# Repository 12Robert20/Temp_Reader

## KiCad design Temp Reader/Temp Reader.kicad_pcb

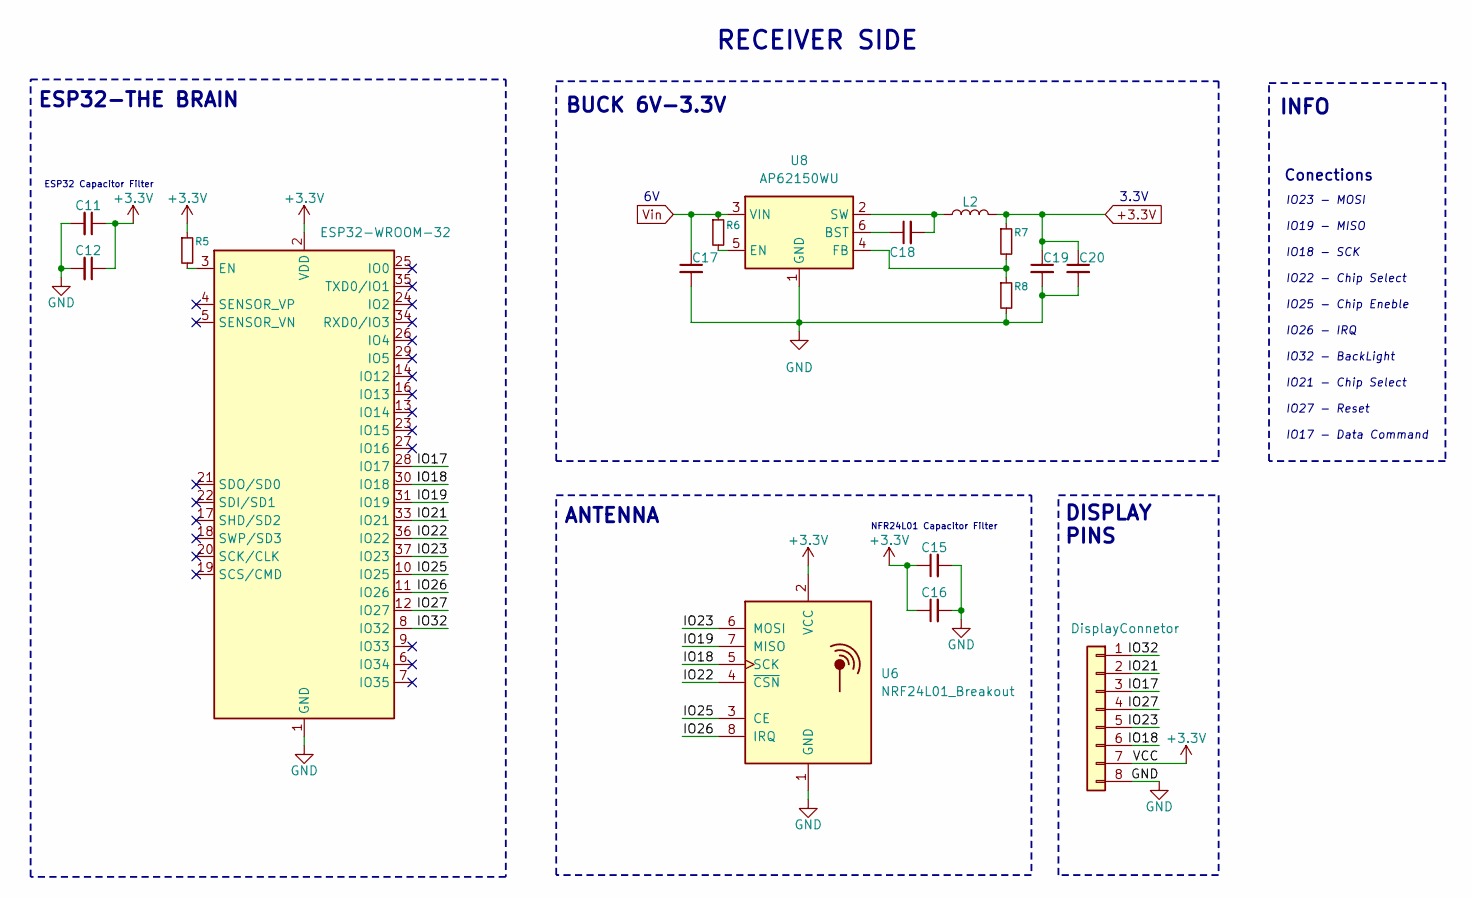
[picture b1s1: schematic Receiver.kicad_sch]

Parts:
C11, C15, C18: 100nF; C_0201_0603Metric
C12, C16: 10uF; C_1206_3216Metric
C17, C19, C20: 22uF; C_1206_3216Metric
J1: DisplayConnetor; PinSocket_1x08_P1.27mm_Vertical
L2: 2.2 uH; L_Bourns-SRN4018
R5, R8: 10k; R_0201_0603Metric
R6: 100k; R_0201_0603Metric
R7: 31.25k; R_0201_0603Metric
U3: ESP32-WROOM-32
U6: NRF24L01_Breakout; nRF24L01_Breakout
U8: AP62150WU; TSOT-23-6

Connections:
+3.3V: C11.1, C12.1, C15.1, C16.1, C19.1, C20.1, J1.7, L2.2, R5.1, R7.1, U3.2 (VDD), U6.2 (VCC); also elsewhere on the board
/Receiver Side/IO18: J1.6, U3.30 (IO18), U6.5 (SCK)
/Receiver Side/IO19: U3.31 (IO19), U6.7 (MISO)
/Receiver Side/IO21: J1.2, U3.33 (IO21)
/Receiver Side/IO22: U3.36 (IO22), U6.4 (~CSN)
/Receiver Side/IO23: J1.5, U3.37 (IO23), U6.6 (MOSI)
/Receiver Side/IO25: U3.10 (IO25), U6.3 (CE)
/Receiver Side/IO26: U3.11 (IO26), U6.8 (IRQ)
/Receiver Side/IO32: J1.1, U3.8 (IO32)
GND: C11.2, C12.2, C15.2, C16.2, C17.2, C19.2, C20.2, J1.8, R8.2, U3.1 (GND), U3.15 (GND), U3.38 (GND), U3.39 (GND), U6.1 (GND), U8.1 (GND); also elsewhere on the board
unnamed: R5.2, U3.3 (EN)
unnamed: C18.1, U8.6 (BST)
unnamed: R6.2, U8.5 (EN)
unnamed: R7.2, R8.1, U8.4 (FB)
unnamed: C18.2, L2.1, U8.2 (SW)
Vin: C17.1, R6.1, U8.3 (VIN); also elsewhere on the board

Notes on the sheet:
DISPLAY PINS
RECEIVER SIDE
IO23 - MOSI IO19 - MISO IO18 - SCK IO22 - Chip Select IO25 - Chip Eneble IO26 - IRQ IO32 - BackLight IO21 - Chip Select IO27 - Reset IO17 - Data Command
INFO
ESP32-THE BRAIN
Conections
ANTENNA
ESP32 Capacitor Filter
3.3V
BUCK 6V-3.3V
NFR24L01 Capacitor Filter

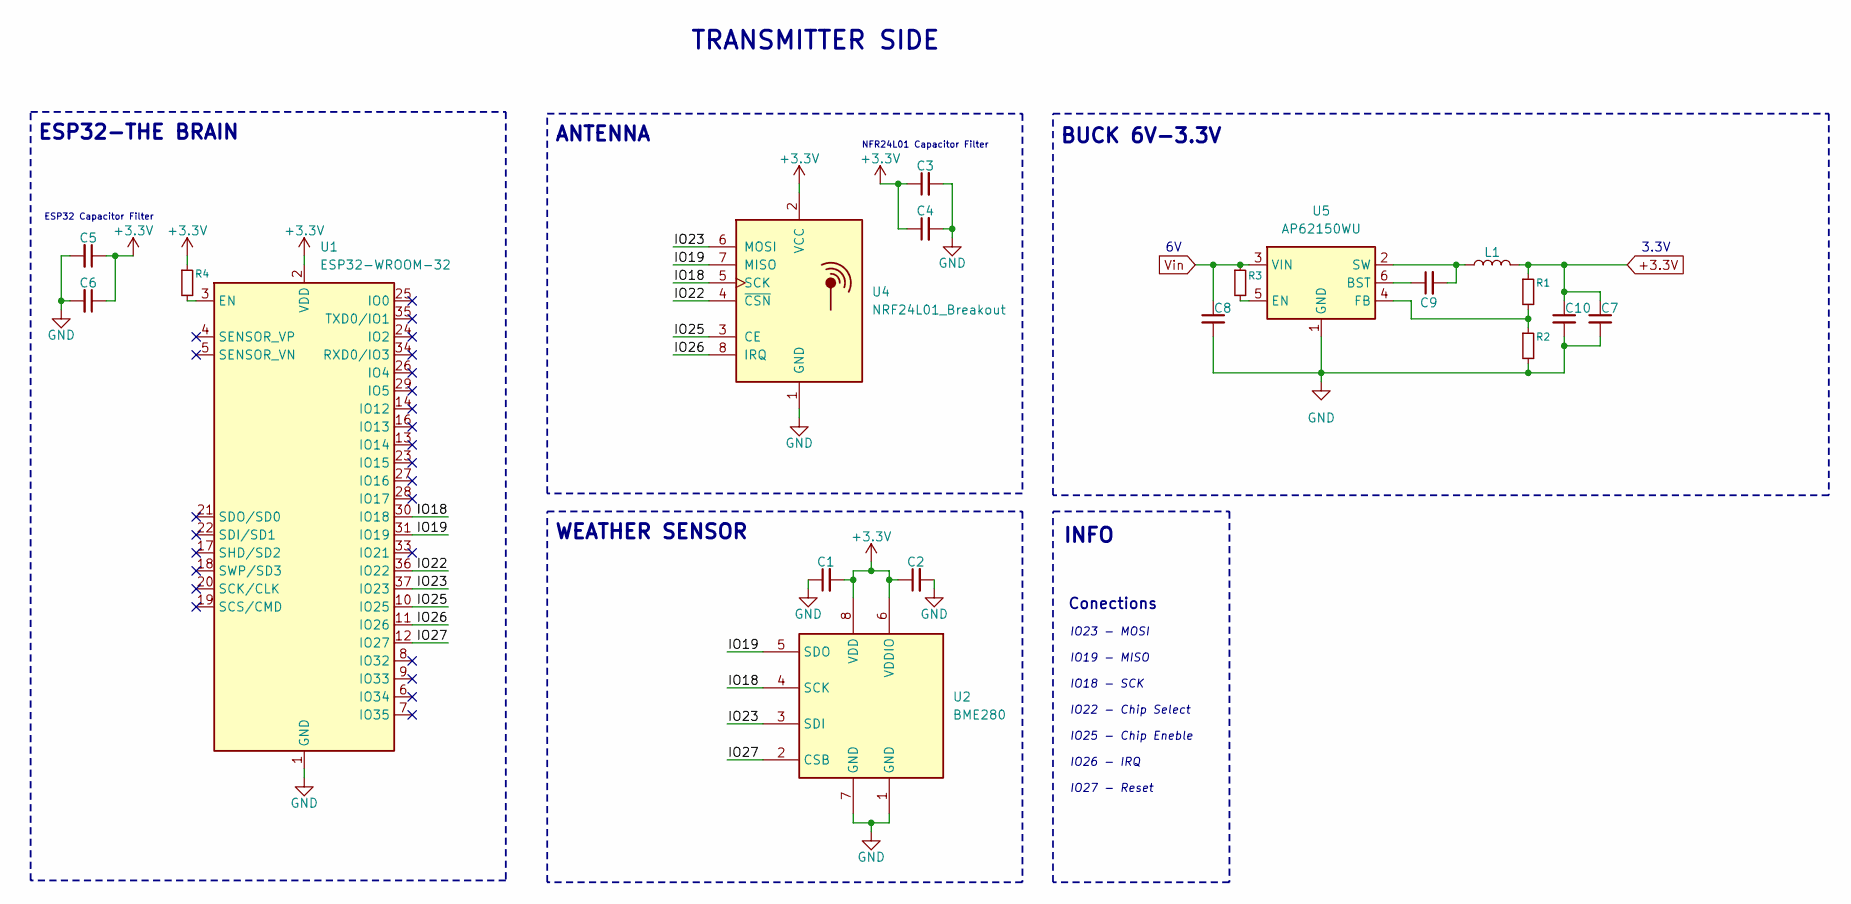
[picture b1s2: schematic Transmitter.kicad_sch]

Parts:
C1, C2, C3, C5, C9: 100nF; C_0201_0603Metric
C4, C6: 10uF; C_1206_3216Metric
C7, C8, C10: 22uF; C_1206_3216Metric
L1: 2.2 uH; L_Bourns-SRN4018
R1: 31.25k; R_0201_0603Metric
R2, R4: 10k; R_0201_0603Metric
R3: 100k; R_0201_0603Metric
U1: ESP32-WROOM-32
U2: BME280; Bosch_LGA-8_2.5x2.5mm_P0.65mm_ClockwisePinNumbering
U4: NRF24L01_Breakout; nRF24L01_Breakout
U5: AP62150WU; TSOT-23-6

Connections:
+3.3V: C1.2, C2.1, C3.1, C4.1, C5.1, C6.1, C7.1, C10.1, L1.2, R1.1, R4.1, U1.2 (VDD), U2.6 (VDDIO), U2.8 (VDD), U4.2 (VCC); also elsewhere on the board
/Transmitter Side/IO18: U1.30 (IO18), U2.4 (SCK), U4.5 (SCK)
/Transmitter Side/IO19: U1.31 (IO19), U2.5 (SDO), U4.7 (MISO)
/Transmitter Side/IO22: U1.36 (IO22), U4.4 (~CSN)
/Transmitter Side/IO23: U1.37 (IO23), U2.3 (SDI), U4.6 (MOSI)
/Transmitter Side/IO25: U1.10 (IO25), U4.3 (CE)
/Transmitter Side/IO26: U1.11 (IO26), U4.8 (IRQ)
/Transmitter Side/IO27: U1.12 (IO27), U2.2 (CSB)
GND: C1.1, C2.2, C3.2, C4.2, C5.2, C6.2, C7.2, C8.2, C10.2, R2.2, U1.1 (GND), U1.15 (GND), U1.38 (GND), U1.39 (GND), U2.1 (GND), U2.7 (GND), U4.1 (GND), U5.1 (GND); also elsewhere on the board
unnamed: R4.2, U1.3 (EN)
unnamed: C9.1, U5.6 (BST)
unnamed: R3.2, U5.5 (EN)
unnamed: R1.2, R2.1, U5.4 (FB)
unnamed: C9.2, L1.1, U5.2 (SW)
Vin: C8.1, R3.1, U5.3 (VIN); also elsewhere on the board

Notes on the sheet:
IO23 - MOSI IO19 - MISO IO18 - SCK IO22 - Chip Select IO25 - Chip Eneble IO26 - IRQ IO27 - Reset
TRANSMITTER SIDE
INFO
Conections
ESP32-THE BRAIN
ANTENNA
ESP32 Capacitor Filter
WEATHER SENSOR
3.3V
BUCK 6V-3.3V
NFR24L01 Capacitor Filter

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
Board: 2 copper layers, 36 parts (0 on the bottom side), 29 nets, no tracks yet.

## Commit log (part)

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2026-06-23 PRIMUL COMMIT CURAT
2026-06-24 1.First Commit
    Save
2026-06-25 2.First Schematic Look
    No Buck
    Raw schematic
2026-06-25 3. 80% schematic done
2026-06-28 Allmost done , pcb start
2026-06-28 **First PCB , Not done yet
